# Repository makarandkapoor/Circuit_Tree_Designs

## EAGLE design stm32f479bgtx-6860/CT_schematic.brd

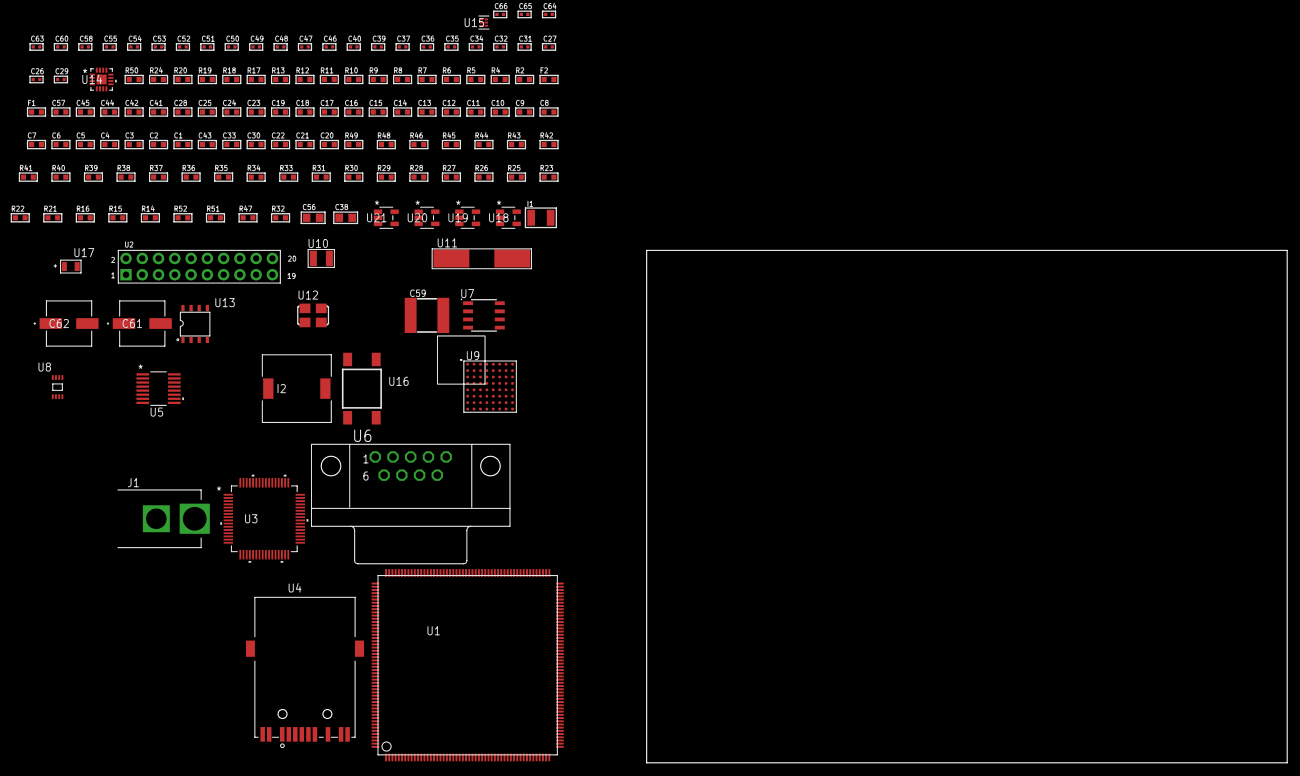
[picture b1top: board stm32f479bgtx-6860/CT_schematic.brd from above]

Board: 2 copper layers, 100.0 x 80.0 mm, 142 parts (0 on the bottom side), 151 nets, no tracks yet.

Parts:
C1, C24, C28, C41, C42, C44, C45, C57: 1e-06; C0603
C2, C3, C4, C5, C6, C7, C8, C9, C10, C11, C12, C13, C14, C15, C16, C17, C18, C19, C25: 1e-07; C0603
C20: 4.7e-06; C0603
C21, C22, C30, C33: 2.2e-06; C0603
C23: 1e-08; C0603
C26, C27: 1e-11; C0402
C29: 1.8e-08; C0402
C31, C34, C36, C37, C39, C40, C48, C50, C52, C58, C60: 1e-07; C0402
C32, C35, C46, C47, C49, C51, C53, C54, C55, C63, C64, C65, C66: 1e-08; C0402
C38, C56: 1e-05; C0805
C43: 2.2e-07; C0603
C59: 6.8e-05; 2220
C61, C62: 0.0001; EXV-9H
F1: 240.0; L0603
F2: 510.0; L0603
I1: 1e-05; L1210
I2: 3.8e-06; DR1040
J1: PJ-037B; PJ-037B_PACKAGE
R2: 1000.0; R0603
R4, R5, R6, R7: 4700.0; R0603
R8, R9, R10, R11, R12, R13: 2200.0; R0603
R14, R15, R16, R21, R22, R23, R25, R26, R27, R28, R29, R30, R31, R33, R34, R35, R36, R37, R38, R39, R40, R41, R42, R43, R44, R48, R49: 10000.0; R0603
R17, R18: 0.1; R0603
R19, R20: 200.0; R0603
R24: 1270.0; R0603
R32: 100000.0; R0603
R45: 20000.0; R0603
R46: 91000.0; R0603
R47: 300000.0; R0603
R50: 9100.0; R0603
R51: 680000.0; R0603
R52: 120000.0; R0603
U1: STM32F479BGT6; LQFP208
U2: arducam_ov2640; ARDUCAM
U3: BCM5221KPT; TQFP64_10X10MC
U4: 7498011122R
U5: LTC2804CGN-1#PBF; SSOP-16
U6: 182-009-113R531; 182-009-MALE
U7: AT24C02D-SSHM-T; AT24C02D
U8: 24AA128T-I/MNY; TDFN-8/6MM
U9: PC28F512P33BFD
U10: ABS07-32.768KHZ-7-T
U11: ABLS-25.000MHZ-B2F-T
U12: ASFL1-25MHZ-NCS; ASFL1
U13: idt74fct38072; IDT74FCT38072
U14: LTC3601EUD#PBF; QFN-16_EP
U15: TPS3895ADRYR; SON-6
U16: 4-1437565-2; SW_4-1437565-2
U17: Q65110A2395; LGM67K-G1J2-24-Z
U18, U19, U20, U21: nc7sz125m5x; NC7SZ125M5X

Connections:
CLK_CRYSTAL_U1_9: C26.1, U1.9, U10.1
CLK_CRYSTAL_U1_10: C27.1, U1.10, U10.2
CLK_CRYSTAL_U3_5: U3.5, U11.2
CLK_CRYSTAL_U3_6: U3.6, U11.1
CLK_U1_32: U1.32, U13.6
CLK_U2_8: U2.8, U13.7
CLK_U13_3: U12.3, U13.3
GND: C1.2, C2.2, C3.2, C4.2, C5.2, C6.2, C7.2, C8.2, C9.2, C10.2, C11.2, C12.2, C13.2, C14.2, C15.2, C16.2, C17.2, C18.2, C19.2, C20.2, C21.2, C22.2, C23.2, C24.2, C25.2, C26.2, C27.2, C28.2, C29.2, C30.2, C31.2, C32.2, C33.2, C34.2, C35.2, C36.2, C37.2, C38.2, C39.2, C40.2, C41.2, C42.2, C44.2, C45.2, C46.2, C47.2, C48.2, C49.2, C50.2, C51.2, C52.2, C53.2, C54.2, C55.2, C56.2, C57.2, C59.1, C59.2, C60.2, C61.2, C62.2, C63.2, C64.2, C65.2, C66.2, J1.2, R2.2, R16.2, R17.2, R18.2, R21.2, R23.2, R24.2, R26.2, R27.2, R28.2, R29.2, R30.2, R33.2, R35.2, R36.2, R38.2, R45.2, R47.2, R50.2, R52.2, U1.14, U1.25, U1.40, U1.51, U1.60, U1.72, U1.82, U1.93, U1.114, U1.122, U1.128, U1.136, U1.149, U1.170, U1.184, U1.202, U2.2, U2.20, U3.7, U3.24, U3.29, U3.32, U3.40, U3.45, U3.54, U3.63, U4.10, U4.12, U5.8, U6.5, U7.4, U8.4, U8.7, U9.B2, U9.H2, U9.H4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
NET_U1_34: R6.1, U1.34, U20.4
NET_U1_36: R12.1, U1.36, U3.42
NET_U1_42: C23.1, C24.1, F1.1, U1.41, U1.42
NET_U1_45: R13.1, U1.45, U3.41
NET_U1_48: R10.1, U1.48, U7.6
NET_U1_49: R11.1, U1.49, U7.5
NET_U1_63: R16.1, U1.63
NET_U1_92: C21.1, U1.92
NET_U1_148: C22.1, U1.148
NET_U1_195: R8.1, U1.195, U8.6
NET_U1_197: R15.1, U1.197
NET_U1_199: R9.1, U1.199, U8.5
NET_U1_203: R14.1, U1.203
NET_U1_206: U16.3, U16.4
NET_U2_19: R7.1, U2.19, U21.4
NET_U3_2: C33.1, C34.1, C35.1, U3.2, U3.55
NET_U3_9: R4.1, U3.9, U18.4
NET_U3_10: R25.1, U3.10
NET_U3_11: R26.1, U3.11
NET_U3_12: R27.1, U3.12
NET_U3_13: R28.1, U3.13
NET_U3_14: R29.1, U3.14
NET_U3_16: R23.1, U3.16
NET_U3_18: R31.1, U3.18
NET_U3_23: R24.1, U3.23
NET_U3_27: C30.1, C31.1, C32.1, U3.22, U3.27, U3.28
NET_U3_37: R30.1, U3.37
NET_U3_38: R21.1, U3.38
NET_U3_39: R22.1, U3.39
NET_U4_1: U3.31, U4.1
NET_U4_2: F2.2, U4.2
NET_U4_3: U3.30, U4.3
NET_U4_4: U3.26, U4.4
NET_U4_5: C29.1, F2.1, U4.2, U4.5
NET_U4_6: U3.25, U4.6
NET_U4_8: R18.1, U4.8
NET_U4_9: R19.1, U4.9
NET_U4_11: R20.1, U4.11
NET_U4_12: R19.2, U4.12
NET_U4_13: R17.1, U4.13, U4.14
NET_U5_6: C41.1, U5.6
NET_U5_7: C43.1, I1.2, U5.7
NET_U5_9: C42.1, U5.9
NET_U5_10: C43.2, U5.10
NET_U5_11: R32.1, U5.11
NET_U6_2: U5.1, U6.2
NET_U6_3: U5.3, U6.3
NET_U6_7: U5.2, U6.7
NET_U6_8: U5.4, U6.8
NET_U7_1: R34.1, U7.1
NET_U7_2: R35.1, U7.2
NET_U7_3: R36.1, U7.3
NET_U7_7: R33.1, U7.7
NET_U8_1: R37.1, U8.1
NET_U8_2: R38.1, U8.2
NET_U8_3: R39.1, U8.3
NET_U9_A4: C52.1, C53.1, U9.A4
NET_U9_C6: R43.1, U9.C6
NET_U9_D4: R5.1, U9.D4, U19.4
NET_U14_3: C58.2, I2.1, U14.3, U14.4
NET_U14_6: C58.1, U14.6
NET_U14_7: C57.1, U14.7, U14.12
NET_U14_10: R47.1, U14.10
NET_U14_11: R45.1, R46.1, U14.11
NET_U14_ATNET_3: I2.2, R46.2
NET_U15_1: R49.1, R50.1, U15.1
NET_U15_3: R51.2, R52.1, U15.3
NET_U15_4: R48.1, U15.4, U18.2, U19.2, U20.2, U21.2
NET_U16_1: R2.1, U16.1, U16.2
PROC_DCMI_D0: U1.99, U2.18
PROC_DCMI_D1: U1.100, U2.17
PROC_DCMI_D2: U1.101, U2.16
PROC_DCMI_D3: U1.102, U2.15
PROC_DCMI_D4: U1.152, U2.14
PROC_DCMI_D5: U1.205, U2.13
PROC_DCMI_D6: U1.207, U2.12
PROC_DCMI_D7: U1.208, U2.11
PROC_DCMI_D8: U1.96, U2.10
PROC_DCMI_D9: U1.97, U2.9
PROC_DCMI_HSYNC: U1.53, U2.6
PROC_DCMI_PIXCLK: U1.55, U2.7
PROC_DCMI_VSYNC: U1.178, U2.5
PROC_ETH_COL: U1.47, U3.61
PROC_ETH_CRS: U1.46, U3.62
PROC_ETH_RXD0: U1.57, U3.48
PROC_ETH_RXD1: U1.58, U3.47
PROC_ETH_RXD2: U1.61, U3.44
PROC_ETH_RX_CLK: U1.44, U3.50
PROC_ETH_RX_DV: U1.56, U3.49
PROC_ETH_RX_ER: U1.12, U3.51
PROC_ETH_TXD2: U1.37, U3.59
PROC_ETH_TX_CLK: U1.38, U3.53
PROC_FMC_A0: U1.16, U9.A1
PROC_FMC_A1: U1.17, U9.B1
PROC_FMC_A2: U1.18, U9.C1
PROC_FMC_A3: U1.22, U9.D1
PROC_FMC_A4: U1.23, U9.D2
PROC_FMC_A5: U1.24, U9.A2
PROC_FMC_A6: U1.71, U9.C2
PROC_FMC_A7: U1.74, U9.A3
PROC_FMC_A8: U1.75, U9.B3
PROC_FMC_A9: U1.76, U9.C3
PROC_FMC_A10: U1.77, U9.D3
PROC_FMC_A11: U1.78, U9.C4
PROC_FMC_A12: U1.129, U9.A5
PROC_FMC_A13: U1.130, U9.B5
PROC_FMC_A14: U1.131, U9.C5
PROC_FMC_A15: U1.132, U9.D7
PROC_FMC_A16: U1.111, U9.D8
PROC_FMC_A17: U1.112, U9.A7
PROC_FMC_A18: U1.113, U9.B7
PROC_FMC_A19: U1.2, U9.C7
PROC_FMC_A20: U1.3, U9.C8
PROC_FMC_A21: U1.4, U9.A8
PROC_FMC_A22: U1.5, U9.G1
PROC_FMC_A23: U1.1, U9.H8
PROC_FMC_A24: U1.182, U9.B6
PROC_FMC_CLK: U1.167, U9.E6
PROC_FMC_D0: U1.116, U9.F2
PROC_FMC_D1: U1.117, U9.E2
PROC_FMC_D2: U1.164, U9.G3
PROC_FMC_D3: U1.165, U9.E4
PROC_FMC_D4: U1.79, U9.E5
PROC_FMC_D5: U1.80, U9.G5
PROC_FMC_D6: U1.81, U9.G6
PROC_FMC_D7: U1.84, U9.H7
PROC_FMC_D8: U1.85, U9.E1
PROC_FMC_D9: U1.86, U9.E3
PROC_FMC_D10: U1.87, U9.F3
PROC_FMC_D11: U1.88, U9.F4
PROC_FMC_D12: U1.89, U9.F5
PROC_FMC_D13: U1.108, U9.H5
PROC_FMC_D14: U1.109, U9.G7
PROC_FMC_D15: U1.110, U9.E7
PROC_FMC_NE2: R41.1, U1.181, U9.B4
PROC_FMC_NL: R40.1, U1.196, U9.F6
PROC_FMC_NOE: R42.1, U1.168, U9.F8
PROC_FMC_NWAIT: U1.172, U9.F7
PROC_FMC_NWE: R44.1, U1.169, U9.G8
PROC_UART4_RX: U1.162, U5.16
PROC_UART4_TX: U1.43, U5.14
VCC_S1_9V2: C56.1, C61.1, C62.1, J1.1, U14.15, U14.16
VCC_TIER1_3V3: C1.1, C2.1, C3.1, C4.1, C5.1, C6.1, C7.1, C8.1, C9.1, C10.1, C11.1, C12.1, C13.1, C14.1, C15.1, C16.1, C17.1, C18.1, C19.1, C20.1, C25.1, C28.1, C36.1, C37.1, C38.1, C39.1, C40.1, C44.1, C45.1, C46.1, C47.1, C48.1, C49.1, C50.1, C51.1, C54.1, C55.1, C59.2, C60.1, C63.1, C64.1, C65.1, C66.1, F1.2, I1.1, I2.2, R4.2, R5.2, R6.2, R7.2, R8.2, R9.2, R10.2, R11.2, R12.2, R13.2, R14.2, R15.2, R22.2, R25.2, R31.2, R32.2, R34.2, R37.2, R39.2, R40.2, R41.2, R42.2, R43.2, R44.2, R46.2, R48.2, R49.2, R51.1, U1.6, U1.15, U1.26, U1.39, U1.52, U1.59, U1.73, U1.83, U1.94, U1.103, U1.115, U1.118, U1.137, U1.150, U1.158, U1.171, U1.185, U1.204, U2.1, U3.1, U3.3, U3.46, U5.5, U5.12, U7.8, U8.8, U9.A6, U9.D5, U9.D6, U9.G4, U9.H3, U12.4, U13.1, U13.2, U14.8, U15.6, U18.5, U19.5, U20.5, U21.5

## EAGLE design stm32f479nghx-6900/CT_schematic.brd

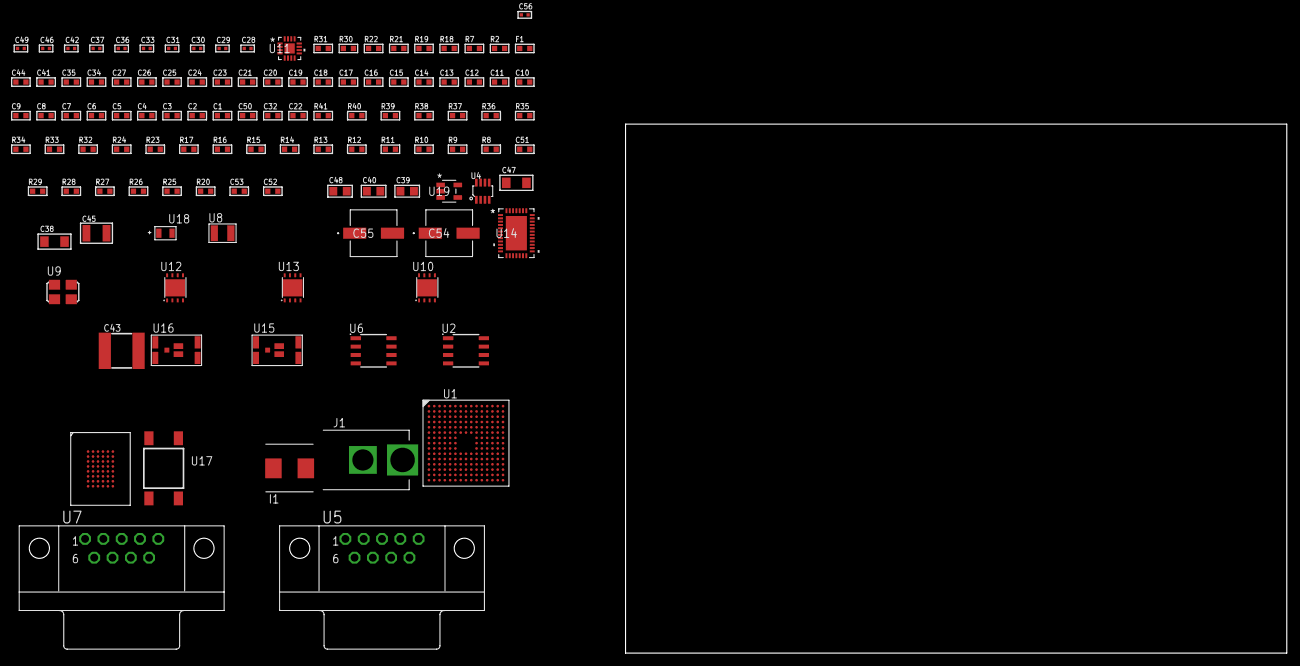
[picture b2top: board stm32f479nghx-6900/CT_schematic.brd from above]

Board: 2 copper layers, 100.0 x 80.0 mm, 114 parts (0 on the bottom side), 101 nets, no tracks yet.

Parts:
C1, C24, C34, C35, C41, C44: 1e-06; C0603
C2, C3, C4, C5, C6, C7, C8, C9, C10, C11, C12, C13, C14, C15, C16, C17, C18, C19, C20, C21, C25, C26, C27: 1e-07; C0603
C22: 4.7e-06; C0603
C23: 1e-08; C0603
C28, C29: 1e-11; C0402
C30, C36, C37, C46, C56: 1e-08; C0402
C31, C33, C42, C49: 1e-07; C0402
C32, C50: 2.2e-06; C0603
C38, C47: 1e-05; C1206
C39, C40, C48: 1e-05; C0805
C43: 6.8e-05; 2220
C45: 1e-05; C1210
C51: 2.45e-08; R0603
C52: 2.8258362168397e-09; R0603
C53: 7.105e-09; R0603
C54, C55: 0.0001; EXV-9H
F1: 240.0; L0603
I1: 3.3e-06; WE-HCI_7030/7040/7050
J1: PJ-037B; PJ-037B_PACKAGE
R2, R22, R31: 1000.0; R0603
R7: 4700.0; R0603
R8, R9, R10, R11, R12, R13, R14, R15, R16, R17, R32, R34, R35, R38, R39, R40: 10000.0; R0603
R18, R19: 120.0; R0603
R20, R26, R28, R29: 100000.0; R0603
R21, R30: 200.0; R0603
R23: 20000.0; R0603
R24: 91000.0; R0603
R25, R27: 300000.0; R0603
R33: 75000.0; R0603
R36, R37: 95300.0; R0603
R41: 62000.0; R0603
U1: STM32F479NGH6; TFBGA216
U2: AT25M02-SSHD-T; SOIC-8
U3: IS61WV102416BLL-10MLI
U4: MAX3051EKA+T; SOT-23-8
U5, U7: 182-009-113R531; 182-009-MALE
U6: MCP2562-E/SN; SOIC-8
U8: ABS07-32.768KHZ-7-T
U9: ASFL1-25MHZ-NCS; ASFL1
U10, U13: LP3878SDX-ADJ/NOPB; WSON-8
U11: LTC3601EUD#PBF; QFN-16_EP
U12: LP2951ACSDX/NOPB; WSON-8
U14: LTC2928CUHF#PBF; QFN-38_UHF
U15, U16: IRF8306MTRPbF; IRF8306MTRPBF
U17: 4-1437565-2; SW_4-1437565-2
U18: Q65110A2395; LGM67K-G1J2-24-Z
U19: nc7sz125m5x; NC7SZ125M5X

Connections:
CLK_CRYSTAL_U1_E1: C28.1, U1.E1, U8.1
CLK_CRYSTAL_U1_F1: C29.1, U1.F1, U8.2
CLK_U1_G1: U1.G1, U9.3
GND: C1.2, C2.2, C3.2, C4.2, C5.2, C6.2, C7.2, C8.2, C9.2, C10.2, C11.2, C12.2, C13.2, C14.2, C15.2, C16.2, C17.2, C18.2, C19.2, C20.2, C21.2, C22.2, C23.2, C24.2, C25.2, C26.2, C27.2, C28.2, C29.2, C30.2, C31.2, C32.2, C33.2, C34.2, C35.2, C36.2, C37.2, C38.2, C39.2, C40.2, C41.2, C43.1, C43.2, C44.2, C45.2, C46.2, C47.2, C48.2, C49.2, C50.2, C51.2, C52.2, C53.2, C54.2, C55.2, C56.2, J1.2, R2.2, R10.2, R22.2, R23.2, R25.2, R28.2, R31.2, R33.2, R36.2, R37.2, R38.2, R39.2, R40.2, U1.F2, U1.F6, U1.F7, U1.F8, U1.F9, U1.F10, U1.G6, U1.G10, U1.G12, U1.H6, U1.H10, U1.J6, U1.J10, U1.K6, U1.K7, U1.K8, U1.K9, U1.K10, U1.L6, U1.M1, U1.N1, U2.4, U3.D1, U3.E6, U4.2, U4.8, U5.5, U6.2, U6.8, U7.5, U9.2, U10.3, U10.PAD, U11.1, U11.9, U11.17, U12.3, U12.4, U12.PAD, U13.3, U13.PAD, U14.8, U14.9, U14.10, U14.12, U14.13, U14.24, U14.25, U14.30, U14.32, U14.39, U18.C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
NET_U1_E5: R8.1, U1.E5
NET_U1_E6: R9.1, U1.E6
NET_U1_E11: C27.1, U1.E11
NET_U1_J1: R7.1, U1.J1, U19.4
NET_U1_L5: R11.1, U1.L5
NET_U1_M5: R10.1, U1.M5
NET_U1_R1: C23.1, C24.1, F1.1, U1.P1, U1.R1
NET_U1_R15: U17.3, U17.4
NET_U2_3: R12.1, U2.3
NET_U2_7: R14.1, U2.7
NET_U3_A2: R16.1, U3.A2
NET_U3_B5: R15.1, U3.B5
NET_U3_G5: R17.1, U3.G5
NET_U4_6: R18.2, U4.6
NET_U5_2: R18.2, U4.6, U5.2
NET_U5_3: R18.1, U4.7, U5.3
NET_U6_6: R19.2, U6.6
NET_U7_2: R19.2, U6.6, U7.2
NET_U7_3: R19.1, U6.7, U7.3
NET_U10_1: C37.1, U10.1
NET_U10_6: R21.2, R22.1, U10.6
NET_U10_8: R20.1, U10.8
NET_U11_3: C42.2, I1.1, U11.3, U11.4
NET_U11_6: C42.1, U11.6
NET_U11_7: C41.1, U11.7, U11.12
NET_U11_10: R25.1, U11.10
NET_U11_11: R23.1, R24.1, U11.11
NET_U11_ATNET_3: I1.2, R24.2
NET_U12_5: R26.1, U12.5
NET_U12_7: R27.2, R28.1, U12.7
NET_U13_1: C46.1, U13.1
NET_U13_6: R30.2, R31.1, U13.6
NET_U13_8: R29.1, U13.8
NET_U14_3: R39.1, U14.3
NET_U14_6: R36.1, U14.6
NET_U14_7: R37.1, U14.7
NET_U14_16: R38.1, R41.1, U14.16
NET_U14_18: R35.1, U14.18
NET_U14_19: R34.1, U14.19, U14.20
NET_U14_21: R32.1, R33.1, U14.21, U19.2
NET_U14_22: C49.1, R32.2, R34.2, R35.2, U14.11, U14.22
NET_U14_26: C52.1, U14.26
NET_U14_27: C51.1, U14.27
NET_U14_28: C53.1, U14.28
NET_U14_38: R40.1, U14.38
NET_U15_3: U14.2, U15.3
NET_U16_3: U14.37, U16.3
NET_U17_1: R2.1, U17.1, U17.2
PROC_CAN1_RX: U1.A7, U6.4
PROC_CAN1_TX: U1.B4, U6.1
PROC_CAN2_RX: U1.L13, U4.4
PROC_CAN2_TX: U1.B6, U4.1
PROC_FMC_A0: U1.D2, U3.A3
PROC_FMC_A1: U1.E2, U3.A4
PROC_FMC_A2: U1.G2, U3.A5
PROC_FMC_A3: U1.H2, U3.B3
PROC_FMC_A4: U1.J2, U3.B4
PROC_FMC_A5: U1.K3, U3.C3
PROC_FMC_A6: U1.M6, U3.C4
PROC_FMC_A7: U1.N6, U3.D4
PROC_FMC_A8: U1.P6, U3.H2
PROC_FMC_A9: U1.M8, U3.H3
PROC_FMC_A10: U1.N7, U3.H4
PROC_FMC_A11: U1.M7, U3.H5
PROC_FMC_A12: U1.M13, U3.G3
PROC_FMC_A13: U1.M12, U3.G4
PROC_FMC_A14: U1.N12, U3.F3
PROC_FMC_A15: U1.N11, U3.F4
PROC_FMC_A16: U1.N10, U3.E4
PROC_FMC_A17: U1.M10, U3.D3
PROC_FMC_A18: U1.M11, U3.H1
PROC_FMC_A19: U1.A2, U3.G2
PROC_FMC_D0: U1.L12, U3.B6
PROC_FMC_D1: U1.K13, U3.C5
PROC_FMC_D2: U1.B12, U3.C6
PROC_FMC_D3: U1.C12, U3.D5
PROC_FMC_D4: U1.R8, U3.E5
PROC_FMC_D5: U1.N9, U3.F5
PROC_FMC_D6: U1.P9, U3.F6
PROC_FMC_D7: U1.R9, U3.G6
PROC_FMC_D8: U1.P10, U3.B1
PROC_FMC_D9: U1.R10, U3.C1
PROC_FMC_D10: U1.R12, U3.C2
PROC_FMC_D11: U1.P11, U3.D2
PROC_FMC_D12: U1.R11, U3.E2
PROC_FMC_D13: U1.L15, U3.F2
PROC_FMC_D14: U1.L14, U3.F1
PROC_FMC_D15: U1.K15, U3.G1
PROC_FMC_NBL0: U1.A6, U3.A1
PROC_SPI1_NSS: R13.1, U2.1
VCC_7V9: C50.1, C54.1, C55.1, J1.1, R41.2, U14.23, U15.1, U15.2, U15.6, U15.7, U16.1, U16.2, U16.6, U16.7
VCC_S1_7V9: C38.1, C40.1, C44.1, R20.2, U10.4, U11.15, U11.16, U12.8, U15.4, U15.5
VCC_S2_7V9: C47.1, R29.2, U13.4, U16.4, U16.5
VCC_TIER1_1V2: C26.1, C39.1, R21.1, U1.L11, U10.5
VCC_TIER1_3V3: C1.1, C2.1, C3.1, C4.1, C5.1, C6.1, C7.1, C8.1, C9.1, C10.1, C11.1, C12.1, C13.1, C14.1, C15.1, C16.1, C17.1, C18.1, C19.1, C20.1, C21.1, C22.1, C25.1, C30.1, C31.1, C32.1, C33.1, C35.1, C36.1, C43.2, C56.1, F1.2, I1.2, R7.2, R8.2, R9.2, R11.2, R12.2, R13.2, R14.2, R15.2, R16.2, R17.2, R24.2, U1.C1, U1.E7, U1.E8, U1.E9, U1.E10, U1.F4, U1.F5, U1.F11, U1.G5, U1.G11, U1.H5, U1.H11, U1.J5, U1.J11, U1.K5, U1.K11, U1.L7, U1.L8, U1.L9, U1.L10, U2.8, U3.D6, U3.E1, U4.3, U6.5, U9.4, U11.8, U19.5
VCC_TIER1_5V0: C34.1, C45.1, R26.2, R27.1, U6.3, U12.1
VCC_TIER2_1V2: C48.1, R30.1, U13.5

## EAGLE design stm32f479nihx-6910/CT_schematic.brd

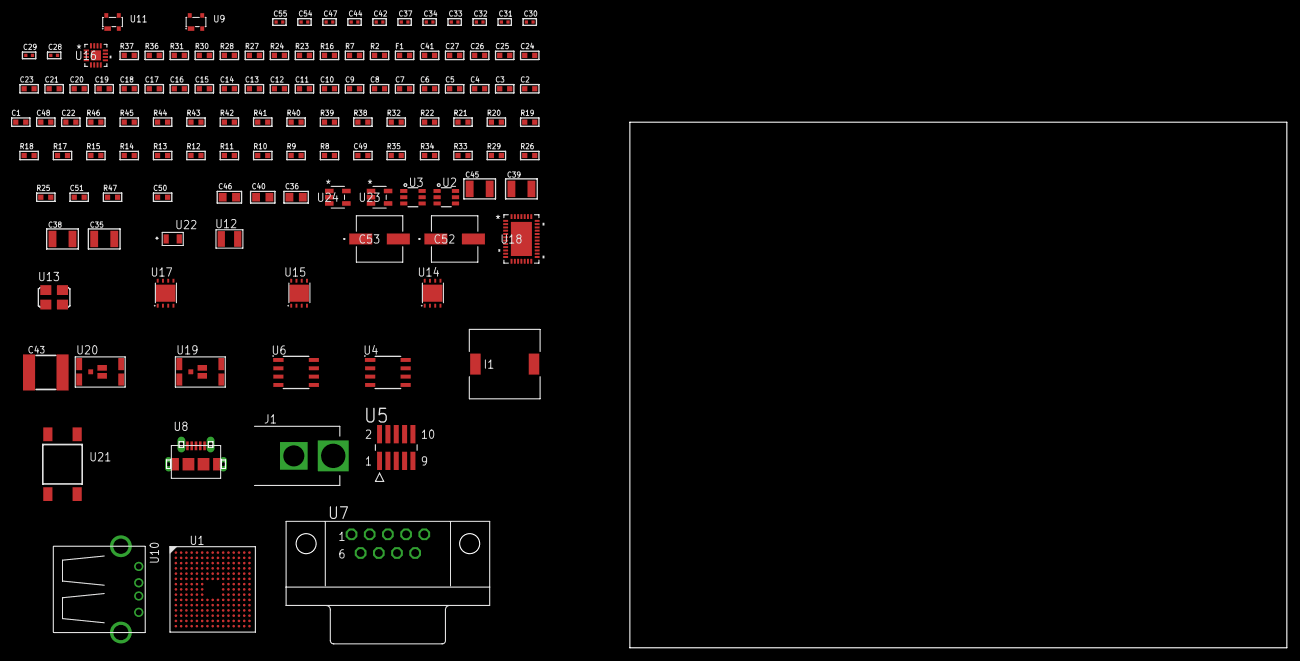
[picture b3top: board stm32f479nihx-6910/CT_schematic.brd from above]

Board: 2 copper layers, 124 parts (0 on the bottom side), 80 nets, no tracks yet.

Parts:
C1, C24, C41: 1e-06; C0603
C2, C3, C4, C5, C6, C7, C8, C9, C10, C11, C12, C13, C14, C15, C16, C17, C18, C19, C20, C21, C25, C26, C27: 1e-07; C0603
C22: 4.7e-06; C0603
C23: 1e-08; C0603
C28, C29: 1e-11; C0402
C30, C33, C34, C37, C44, C54, C55: 1e-08; C0402
C31, C32, C42, C47: 1e-07; C0402
C35, C38, C39, C45: 1e-05; C1210
C36, C40, C46: 1e-05; C0805
C43: 6.8e-05; 2220
C48: 2.2e-06; C0603
C49: 2.45e-08; R0603
C50: 2.8258362168397e-09; R0603
C51: 7.105e-09; R0603
C52, C53: 0.0001; EXV-9H
F1: 240.0; L0603
I1: 7e-06; DR1040
J1: PJ-037B; PJ-037B_PACKAGE
R2, R28, R31, R37: 1000.0; R0603
R7: 4700.0; R0603
R8, R9: 47000.0; R0603
R10, R11, R12, R13, R14, R15, R17, R18, R19, R20, R21, R22, R38, R40, R41, R44, R45, R46: 10000.0; R0603
R16: 1270.0; R0603
R23: 5.0; R0603
R24: 120.0; R0603
R25: 470000.0; R0603
R26, R29, R35: 100000.0; R0603
R27, R36: 200.0; R0603
R30: 2231.0; R0603
R32: 20000.0; R0603
R33: 150000.0; R0603
R34: 300000.0; R0603
R39: 75000.0; R0603
R42, R43: 95300.0; R0603
R47: 113145.45454545; R0603
U1: STM32F479NIH6; TFBGA216
U2, U3: MAX4995AAUT+T; SOT-23-6
U4: AT25160B-SSHL-T; SOIC-8
U5: FTSH-105-01-L-DV-K; SAMTEC_FTSH-105-01-L-DV-K
U6: SN65HVD230D; SOIC-8
U7: 182-009-113R531; 182-009-MALE
U8: 47590-0001; MICRO_USB_AB
U9, U11: prtr5v0u2ax; SOT143B
U10: 61400416021; USB-A-H
U12: ABS07-32.768KHZ-7-T
U13: ASFL1-25MHZ-NCS; ASFL1
U14, U15, U17: LP3878SDX-ADJ/NOPB; WSON-8
U16: LTC3601EUD#PBF; QFN-16_EP
U18: LTC2928CUHF#PBF; QFN-38_UHF
U19, U20: IRF8306MTRPbF; IRF8306MTRPBF
U21: 4-1437565-2; SW_4-1437565-2
U22: Q65110A2395; LGM67K-G1J2-24-Z
U23, U24: nc7sz125m5x; NC7SZ125M5X

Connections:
CLK_CRYSTAL_U1_E1: C28.1, U1.E1, U12.1
CLK_CRYSTAL_U1_F1: C29.1, U1.F1, U12.2
CLK_U1_G1: U1.G1, U13.3
GND: C1.2, C2.2, C3.2, C4.2, C5.2, C6.2, C7.2, C8.2, C9.2, C10.2, C11.2, C12.2, C13.2, C14.2, C15.2, C16.2, C17.2, C18.2, C19.2, C20.2, C21.2, C22.2, C23.2, C24.2, C25.2, C26.2, C27.2, C28.2, C29.2, C30.2, C31.2, C32.2, C33.2, C34.2, C35.2, C36.2, C37.2, C38.2, C39.2, C40.2, C41.2, C43.1, C43.2, C44.2, C45.2, C46.2, C47.2, C48.2, C49.2, C50.2, C51.2, C52.2, C53.2, C54.2, C55.2, J1.2, R2.2, R8.2, R9.2, R15.2, R16.2, R23.2, R25.2, R28.2, R31.2, R32.2, R34.2, R37.2, R39.2, R42.2, R43.2, R44.2, R45.2, R46.2, U1.F2, U1.F6, U1.F7, U1.F8, U1.F9, U1.F10, U1.G6, U1.G10, U1.G12, U1.H6, U1.H10, U1.J6, U1.J10, U1.K6, U1.K7, U1.K8, U1.K9, U1.K10, U1.L6, U1.L13, U1.M1, U1.N1, U2.2, U3.2, U4.4, U5.3, U5.5, U6.2, U7.5, U8.5, U8.6, U8.7, U8.8, U8.9, U9.1, U10.4, U10.5, U10.6, U11.1, U13.2, U14.3, U14.PAD, U15.3, U15.PAD, U16.1, U16.9, U16.17, U17.3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
NET_U1_E5: R10.1, U1.E5
NET_U1_E6: R11.1, U1.E6
NET_U1_E11: C27.1, U1.E11
NET_U1_J1: R7.1, U1.J1, U24.4
NET_U1_L5: R13.1, U1.L5
NET_U1_L13: R16.1, U1.L13
NET_U1_M5: R12.1, U1.M5
NET_U1_R1: C23.1, C24.1, F1.1, U1.P1, U1.R1
NET_U1_R13: U21.3, U21.4
NET_U2_3: R8.1, U2.3
NET_U3_3: R9.1, U3.3
NET_U4_3: R17.1, U4.3
NET_U4_7: R19.1, U4.7
NET_U5_9: R23.1, U5.9
NET_U6_6: R24.2, U6.6
NET_U6_8: R25.1, U6.8
NET_U7_2: R24.2, U6.6, U7.2
NET_U7_3: R24.1, U6.7, U7.3
NET_U14_1: C34.1, U14.1
NET_U14_6: R27.2, R28.1, U14.6
NET_U14_8: R26.1, U14.8
NET_U15_1: C37.1, U15.1
NET_U15_6: R30.2, R31.1, U15.6
NET_U15_8: R29.1, U15.8
NET_U16_3: C42.2, I1.1, U16.3, U16.4
NET_U16_6: C42.1, U16.6
NET_U16_7: C41.1, U16.7, U16.12
NET_U16_10: R34.1, U16.10
NET_U16_11: R32.1, R33.1, U16.11
NET_U16_ATNET_3: I1.2, R33.2
NET_U17_1: C44.1, U17.1
NET_U17_6: R36.2, R37.1, U17.6
NET_U17_8: R35.1, U17.8
NET_U18_3: R45.1, U18.3
NET_U18_6: R42.1, U18.6
NET_U18_7: R43.1, U18.7
NET_U18_16: R44.1, R47.1, U18.16
NET_U18_18: R41.1, U18.18
NET_U18_19: R40.1, U18.19, U18.20
NET_U18_21: R38.1, R39.1, U18.21, U23.4, U24.2
NET_U18_22: C47.1, R38.2, R40.2, R41.2, U18.11, U18.22
NET_U18_26: C50.1, U18.26
NET_U18_27: C49.1, U18.27
NET_U18_28: C51.1, U18.28
NET_U18_38: R46.1, U18.38
NET_U19_3: U18.2, U19.3
NET_U20_3: U18.37, U20.3
NET_U21_1: R2.1, U21.1, U21.2
PROC_CAN1_RX: U1.A7, U6.4
PROC_CAN1_TX: U1.B4, U6.1
PROC_GPIO_TO_U1_USB_FAULT: R14.1, U1.A2, U2.6
PROC_GPIO_TO_U1_USB_FAULT2: U1.A4, U3.6
PROC_GPIO_TO_U1_VBUS_EN: R15.1, U1.A1, U2.4
PROC_GPIO_TO_U1_VBUS_EN2: U1.A3, U3.4
PROC_SPI1_MISO: U1.A9, U4.2
PROC_SPI1_MOSI: U1.A8, U4.5
PROC_SPI1_NSS: R18.1, U1.A13, U4.1
PROC_SPI1_SCK: U1.P4, U4.6
PROC_SYS_JTCK_SWCLK: R21.1, U1.A14, U5.4
PROC_SYS_JTDO_SWO: U1.A10, U5.6
PROC_SYS_JTMS_SWDIO: R22.1, U1.A15, U5.2
PROC_USB_OTG_FS_DM: U1.C15, U8.2, U9.3
PROC_USB_OTG_FS_DP: U1.B15, U8.3, U9.2
PROC_USB_OTG_FS_ID: U1.D15, U8.4
PROC_USB_OTG_FS_VBUS: U1.E15, U2.1, U8.1, U9.4
PROC_USB_OTG_HS_DM: U1.R14, U10.2, U11.3
PROC_USB_OTG_HS_DP: U1.R15, U10.3, U11.2
PROC_USB_OTG_HS_VBUS: U1.K14, U3.1, U10.1, U11.4
RST_OUT_U5_JTAG_RST_B: R20.1, U5.10, U23.1
VCC_13V8: C48.1, C52.1, C53.1, J1.1, R47.2, U18.23, U19.1, U19.2, U19.6, U19.7, U20.1, U20.2, U20.6, U20.7
VCC_S1_13V8: C35.1, C38.1, C40.1, R26.2, R29.2, U14.4, U15.4, U16.15, U16.16, U19.4, U19.5
VCC_S2_13V8: C45.1, R35.2, U17.4, U20.4, U20.5
VCC_TIER1_1V2: C26.1, C36.1, R27.1, U1.L11, U14.5
VCC_TIER1_3V3: C1.1, C2.1, C3.1, C4.1, C5.1, C6.1, C7.1, C8.1, C9.1, C10.1, C11.1, C12.1, C13.1, C14.1, C15.1, C16.1, C17.1, C18.1, C19.1, C20.1, C21.1, C22.1, C25.1, C30.1, C31.1, C32.1, C33.1, C39.1, C54.1, C55.1, F1.2, R7.2, R10.2, R11.2, R12.2, R13.2, R14.2, R17.2, R18.2, R19.2, R20.2, R21.2, R22.2, R30.1, U1.C1, U1.E7, U1.E8, U1.E9, U1.E10, U1.F4, U1.F5, U1.F11, U1.G5, U1.G11, U1.H5, U1.H11, U1.J5, U1.J11, U1.K5, U1.K11, U1.L7, U1.L8, U1.L9, U1.L10, U4.8, U5.1, U6.3, U13.4, U15.5, U23.5, U24.5
VCC_TIER1_5V0: C43.2, I1.2, R33.2, U2.5, U3.5, U16.8
VCC_TIER2_1V2: C46.1, R36.1, U17.5

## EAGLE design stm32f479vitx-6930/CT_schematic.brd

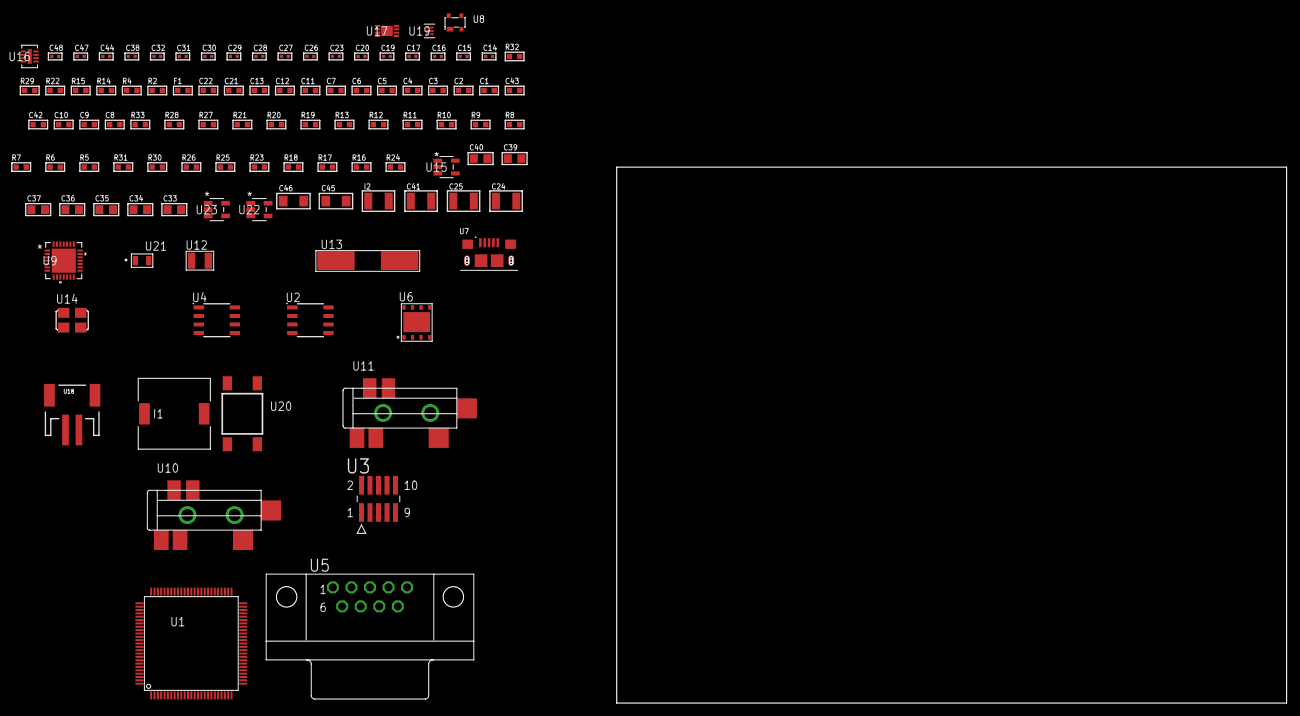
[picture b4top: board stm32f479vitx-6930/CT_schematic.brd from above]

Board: 2 copper layers, 122.6 x 80.0 mm, 104 parts (0 on the bottom side), 63 nets, no tracks yet.

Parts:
C1, C12, C21, C22: 1e-06; C0603
C2, C3, C4, C5, C6, C7, C13: 1e-07; C0603
C8: 4.7e-06; C0603
C9, C10, C42: 2.2e-06; C0603
C11: 1e-08; C0603
C14, C15, C16, C17: 1e-11; C0402
C19, C38, C47, C48: 1e-08; C0402
C20, C23, C28, C29, C30, C31, C32, C44: 1e-07; C0402
C24, C25: 2.2e-05; C1210
C26, C27: 1e-09; C0402
C33, C34, C35, C36, C37, C39, C40: 1e-05; C0805
C41: 1e-05; C1210
C43: 2.2e-07; C0603
C45, C46: 1e-05; C1206
F1: 240.0; L0603
I1: 2.5e-06; DR1040
I2: 1e-05; L1210
R2: 1000.0; R0603
R4: 4700.0; R0603
R5, R6, R7, R8, R9, R10, R11, R12, R13, R27, R28, R33: 10000.0; R0603
R14: 5.0; R0603
R15: 120.0; R0603
R16, R17, R18, R25: 100000.0; R0603
R19, R20, R21: 47000.0; R0603
R22: 680.0; R0603
R23: 220000.0; R0603
R24: 1000000.0; R0603
R26: 560000.0; R0603
R29: 9100.0; R0603
R30: 680000.0; R0603
R31: 120000.0; R0603
R32: 2000.0; R0603
U1: STM32F479VIT6; LQFP100
U2: AT25M01-SSHM-T; SOIC-8
U3: FTSH-105-01-L-DV-K; SAMTEC_FTSH-105-01-L-DV-K
U4: MCP2562-E/SN; SOIC-8
U5: 182-009-113R531; 182-009-MALE
U6: SST26VF032B-104I/MF; WFDN-8
U7: 10118193-0001LF; FCI_10118193-0001LF
U8: prtr5v0u2ax; SOT143B
U9: WM8731CLSEFL; QFN-28
U10, U11: SJ-43515TS-SMT-TR
U12: ABS07-32.768KHZ-7-T
U13: ABLS-25.000MHZ-B2F-T
U14: ASFL1-12.288MHZ-EC-T; ASFL1
U15: ltc3406es5; TSOT-23-5
U16: LT3494AEDDB#TRMPBF; DFN-8_DDB
U17: MCP73831T-2ACI/MC; DFN8_2X3MC
U18: S2B-PH-SM4-TB(LF)(SN); JST-2-SMD
U19: TPS3895ADRYR; SON-6
U20: 4-1437565-2; SW_4-1437565-2
U21: Q65110A2395; LGM67K-G1J2-24-Z
U22, U23: nc7sz125m5x; NC7SZ125M5X

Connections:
CLK_CRYSTAL_U1_5: C14.1, U1.5, U12.1
CLK_CRYSTAL_U1_6: C15.1, U1.6, U12.2
CLK_CRYSTAL_U1_9: C16.1, U1.9, U13.1
CLK_CRYSTAL_U1_10: C17.1, U1.10, U13.2
CLK_U9_1: U9.1, U14.3
GND: C1.2, C2.2, C3.2, C4.2, C5.2, C6.2, C7.2, C8.2, C9.2, C10.2, C11.2, C12.2, C13.2, C14.2, C15.2, C16.2, C17.2, C19.2, C20.2, C21.2, C22.2, C23.2, C27.2, C28.2, C29.2, C30.2, C31.2, C32.2, C33.2, C34.2, C35.2, C36.2, C37.2, C38.2, C39.2, C40.1, C40.2, C41.2, C42.2, C43.2, C44.2, C45.2, C46.2, C47.2, C48.2, R2.2, R13.2, R14.2, R19.2, R20.2, R21.2, R23.2, R29.2, R31.2, R32.2, U1.2, U1.7, U1.16, U1.23, U1.44, U1.59, U1.78, U2.4, U3.3, U3.5, U4.2, U4.8, U5.5, U6.4, U6.9, U7.5, U7.6, U7.7, U7.8, U7.9, U8.1, U9.4, U9.15, U9.19, U9.25, U9.26, U9.29, U10.1, U11.1, U14.2, U15.2, U16.2, U16.9, U17.6, U17.9, U18.2, U19.2, U21.C, U22.2, U22.3, U23.1, U23.3
INPUT_USBPOWER_5V: C45.1, R33.2, U7.1, U8.4, U17.1, U17.2
NET_U1_11: R4.1, U1.11, U23.4
NET_U1_18: C11.1, C12.1, F1.1, U1.17, U1.18
NET_U1_31: R6.1, U1.31
NET_U1_43: C9.1, U1.43
NET_U1_76: C10.1, U1.76
NET_U1_97: R5.1, U1.97
NET_U1_99: U20.3, U20.4
NET_U2_3: R7.1, U2.3
NET_U2_7: R9.1, U2.7
NET_U3_9: R14.1, U3.9
NET_U4_6: R15.2, U4.6
NET_U5_2: R15.2, U4.6, U5.2
NET_U5_3: R15.1, U4.7, U5.3
NET_U9_20: C32.1, C37.1, U9.20
NET_U10_2: C25.1, R20.1, U10.2
NET_U10_5: C24.1, R19.1, U10.5
NET_U11_5: C26.1, C27.1, R21.1, R22.1, U11.5
NET_U15_3: I1.1, U15.3
NET_U15_5: R23.1, R24.1, U15.5
NET_U15_ATNET_3: I1.2, R24.2
NET_U16_1: I2.1, U16.1
NET_U16_5: R25.1, U16.5
NET_U16_6: R26.1, U16.6
NET_U16_8: C43.1, U16.8
NET_U17_5: R33.1, U17.5
NET_U17_8: R32.1, U17.8
NET_U19_1: R28.1, R29.1, U19.1
NET_U19_3: R30.2, R31.1, U19.3
NET_U19_4: R27.1, U19.4, U22.4, U23.2
NET_U20_1: R2.1, U20.1, U20.2
PROC_CAN1_RX: U1.84, U4.4
PROC_CAN1_TX: U1.85, U4.1
PROC_I2S2_CK: U1.47, U9.7
PROC_I2S2_EXT_SD: U1.14, U9.10
PROC_I2S2_SD: U1.13, U9.8
PROC_I2S2_WS: U1.46, U9.9, U9.11
PROC_QUADSPI_BK1_IO0: U1.69, U6.5
PROC_QUADSPI_BK1_IO1: U1.81, U6.2
PROC_QUADSPI_BK1_IO2: R17.1, U1.1, U6.3
PROC_QUADSPI_BK1_IO3: R18.1, U1.20, U6.7
PROC_QUADSPI_BK1_NCS: R16.1, U1.41, U6.1
PROC_QUADSPI_CLK: U1.28, U6.6
PROC_SPI1_MISO: U1.27, U2.2
PROC_SPI1_MOSI: U1.94, U2.5
PROC_SPI1_NSS: R8.1, U1.25, U2.1
PROC_SPI1_SCK: U1.26, U2.6
PROC_SYS_JTCK_SWCLK: R13.1, U1.79, U3.4
PROC_SYS_JTDI: R11.1, U1.80, U3.8
PROC_SYS_JTDO_SWO: U1.92, U3.6
PROC_SYS_JTMS_SWDIO: R12.1, U1.75, U3.2
PROC_USB_OTG_FS_DM: U7.2, U8.3
PROC_USB_OTG_FS_DP: U7.3, U8.2
RST_OUT_U3_JTAG_RST_B: R10.1, U3.10, U22.1
VCC_S1_3V7: C39.1, C41.1, C46.1, I2.2, R25.2, U15.4, U16.3, U16.4, U17.3, U17.4, U18.1
VCC_TIER1_3V3: C1.1, C2.1, C3.1, C4.1, C5.1, C6.1, C7.1, C8.1, C13.1, C19.1, C20.1, C22.1, C23.1, C28.1, C29.1, C30.1, C31.1, C33.1, C34.1, C35.1, C36.1, C38.1, C40.2, C44.1, C47.1, C48.1, F1.2, I1.2, R4.2, R5.2, R6.2, R7.2, R8.2, R9.2, R10.2, R11.2, R12.2, R16.2, R17.2, R18.2, R24.2, R27.2, R28.2, R30.1, U1.3, U1.8, U1.24, U1.45, U1.55, U1.65, U1.77, U1.100, U2.8, U3.1, U4.5, U6.8, U9.3, U9.5, U9.12, U9.18, U14.4, U19.6, U22.5, U23.5
VCC_TIER1_5V0: C21.1, C42.1, R26.2, U4.3, U16.7

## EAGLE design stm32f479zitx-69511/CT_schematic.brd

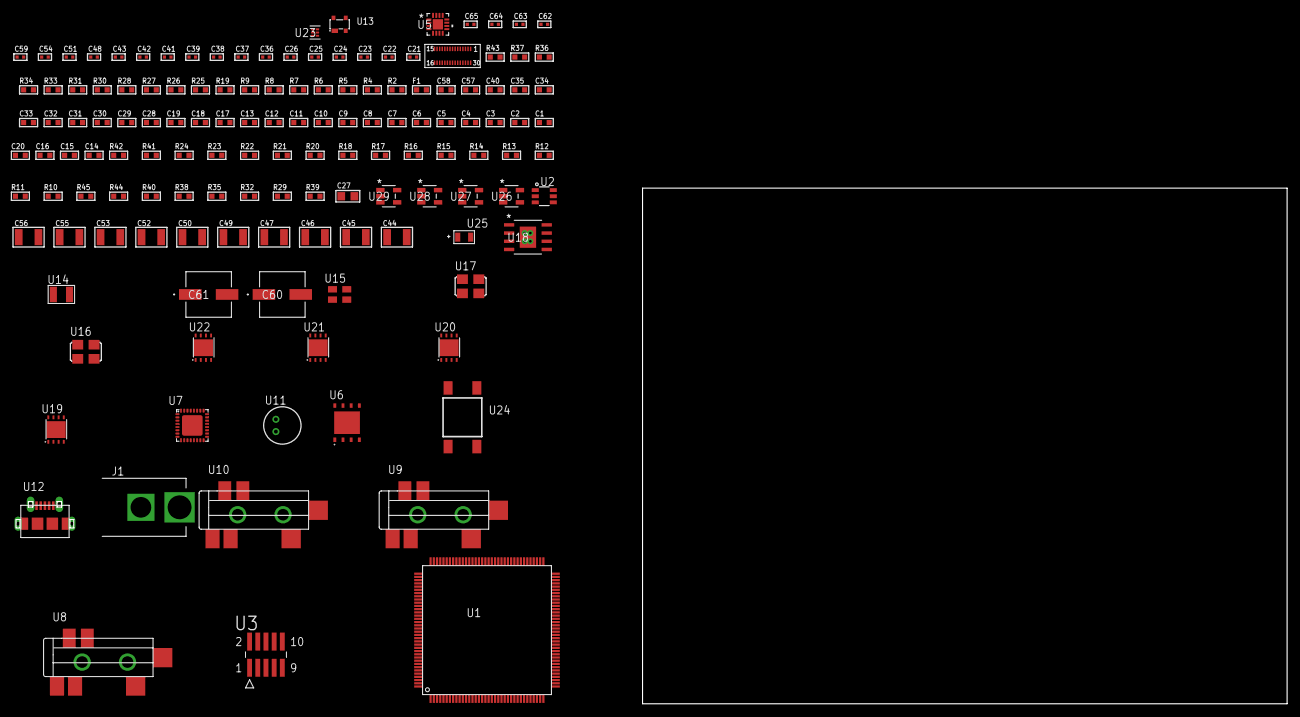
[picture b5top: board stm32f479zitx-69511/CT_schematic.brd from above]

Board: 2 copper layers, 139 parts (0 on the bottom side), 85 nets, no tracks yet.

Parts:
C1, C18, C28, C29, C30, C31, C32, C33, C34, C35, C40: 1e-06; C0603
C2, C3, C4, C5, C6, C7, C8, C9, C10, C11, C12, C13, C19: 1e-07; C0603
C14: 4.7e-06; C0603
C15, C16, C20: 2.2e-06; C0603
C17: 1e-08; C0603
C21, C22, C23, C24, C25, C26, C36, C37, C38, C39, C59: 1e-07; C0402
C27: 4.7e-06; C0805
C41, C42, C43, C48, C51, C54, C62, C63, C64, C65: 1e-08; C0402
C44, C45, C46, C47, C49, C50, C52, C53, C55, C56: 1e-05; C1210
C57: 8e-07; R0603
C58: 8e-06; R0603
C60, C61: 0.0001; EXV-9H
F1: 240.0; L0603
J1: PJ-037B; PJ-037B_PACKAGE
R2, R31, R34, R37: 1000.0; R0603
R4, R5, R6: 4700.0; R0603
R7, R8, R9, R28: 2200.0; R0603
R10: 47000.0; R0603
R11, R12, R13, R14, R15, R16, R17, R18, R20, R21, R22, R23, R24, R41, R42: 10000.0; R0603
R19: 5.0; R0603
R25, R26: 1270.0; R0603
R27: 910.0; R0603
R29, R32, R35, R38, R40: 100000.0; R0603
R30: 1800.0; R0603
R33: 2231.0; R0603
R36: 3900.0; R0603
R39: 842943.08; R0603
R43: 9100.0; R0603
R44: 680000.0; R0603
R45: 120000.0; R0603
U1: STM32F479ZIT6; LQFP144
U2: MAX4995AAUT+T; SOT-23-6
U3: FTSH-105-01-L-DV-K; SAMTEC_FTSH-105-01-L-DV-K
U4: LH430WV2-SD01
U5: M41T65Q6F; M41T65_QFN-16
U6: MX25R6435FZAIH0; WSON-8-PAD
U7: SGTL5000XNAA3; QFN-32
U8, U9, U10: SJ-43515TS-SMT-TR
U11: WM-64PCT; WM-64PC
U12: 47590-0001; MICRO_USB_AB
U13: prtr5v0u2ax; SOT143B
U14: ABS07-32.768KHZ-7-T
U15: ASEK-32.768KHz-ECST; ASEK
U16: ASFL-24.57MHZ-NCS; ASFL1
U17: ASFL1-25MHZ-NCS; ASFL1
U18: MIC5234YME; SOIC-8_EP
U19, U20, U21: LP3878SDX-ADJ/NOPB; WSON-8
U22: LP2951ACSDX/NOPB; WSON-8
U23: TPS3895ADRYR; SON-6
U24: 4-1437565-2; SW_4-1437565-2
U25: Q65110A2395; LGM67K-G1J2-24-Z
U26, U27, U28, U29: nc7sz125m5x; NC7SZ125M5X

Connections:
CLK_CRYSTAL_U5_1: U5.1, U14.1
CLK_CRYSTAL_U5_2: U5.2, U14.2
CLK_U1_7: U1.7, U15.3
CLK_U1_18: U1.18, U17.3
CLK_U7_21: U7.21, U16.3
GND: C1.2, C2.2, C3.2, C4.2, C5.2, C6.2, C7.2, C8.2, C9.2, C10.2, C11.2, C12.2, C13.2, C14.2, C15.2, C16.2, C17.2, C18.2, C19.2, C21.2, C22.2, C23.2, C24.2, C25.2, C26.2, C27.2, C28.2, C36.2, C37.2, C38.2, C39.2, C40.2, C41.2, C42.2, C43.2, C44.2, C45.2, C46.2, C47.2, C48.2, C49.2, C50.2, C51.2, C52.2, C53.2, C54.2, C55.2, C56.2, C57.2, C58.2, C59.2, C60.2, C61.2, C62.2, C63.2, C64.2, C65.2, J1.2, R2.2, R10.2, R13.2, R15.2, R19.2, R20.2, R26.2, R28.2, R31.2, R34.2, R37.2, R40.2, R43.2, R45.2, U1.15, U1.26, U1.33, U1.55, U1.76, U1.109, U1.122, U1.129, U2.2, U3.3, U3.5, U4.1, U4.6, U4.9, U4.12, U4.15, U4.17, U4.18, U4.19, U4.24, U4.27, U5.3, U5.5, U5.17, U6.4, U6.PAD, U7.1, U7.3, U7.7, U7.EXP, U9.1, U10.1, U11.2, U12.5, U12.6, U12.7, U12.8, U12.9, U13.1, U15.2, U16.2, U17.2, U18.7, U18.EPAD, U19.3, U19.PAD, U20.3, U20.PAD, U21.3, U21.PAD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
NET_U1_20: R6.1, U1.20, U29.4
NET_U1_28: C17.1, C18.1, F1.1, U1.27, U1.28
NET_U1_43: R13.1, U1.43
NET_U1_65: C15.1, U1.65
NET_U1_84: C20.2, U1.84
NET_U1_87: C20.1, U1.81, U1.87
NET_U1_108: C16.1, U1.108
NET_U1_135: R7.1, U1.135, U5.10
NET_U1_136: R8.1, U1.136, U5.9
NET_U1_137: R12.1, U1.137
NET_U1_141: U24.3, U24.4
NET_U1_142: R11.1, U1.142
NET_U2_3: R10.1, U2.3
NET_U3_9: R19.1, U3.9
NET_U4_4: R4.1, U4.4, U27.4
NET_U4_20: R20.1, U4.20
NET_U5_4: R21.1, U5.4
NET_U5_11: R22.1, U5.11
NET_U6_7: R5.1, U1.30, U6.7, U28.4
NET_U7_10: C39.1, U7.10
NET_U7_29: R25.1, U7.29
NET_U7_31: R26.1, U7.31
NET_U8_1: U7.4, U8.1
NET_U8_2: U7.2, U8.2
NET_U8_5: U7.6, U8.5
NET_U9_2: C30.1, U9.2
NET_U9_5: C29.1, U9.5
NET_U10_2: C32.1, C33.1, U10.2
NET_U10_5: C31.1, U10.5
NET_U10_13: C32.2, C33.2
NET_U11_1: C34.1, C35.1, C40.1, U7.16, U11.1
NET_U11_15: C34.2, C35.2
NET_U18_4: R27.2, R28.1, U18.4
NET_U19_1: C48.1, U19.1
NET_U19_6: R30.2, R31.1, U19.6
NET_U19_8: R29.1, U19.8
NET_U20_1: C51.1, U20.1
NET_U20_6: R33.2, R34.1, U20.6
NET_U20_8: R32.1, U20.8
NET_U21_1: C54.1, U21.1
NET_U21_6: R36.2, R37.1, U21.6
NET_U21_8: R35.1, U21.8
NET_U22_5: R38.1, U22.5
NET_U22_7: R39.2, R40.1, U22.7
NET_U23_1: R42.1, R43.1, U23.1
NET_U23_3: R44.2, R45.1, U23.3
NET_U23_4: R41.1, U23.4, U26.4, U27.2, U28.2, U29.2
NET_U24_1: R2.1, U24.1, U24.2
PROC_DSIHOST_CKN: U1.86, U4.13
PROC_DSIHOST_CKP: U1.85, U4.14
PROC_DSIHOST_D0N: U1.83, U4.7
PROC_DSIHOST_D0P: U1.82, U4.8
PROC_DSIHOST_D1N: U1.89, U4.10
PROC_DSIHOST_D1P: U1.88, U4.11
PROC_GPIO_TO_U1_USB_FAULT: R14.1, U1.2, U2.6
PROC_GPIO_TO_U1_VBUS_EN: R15.1, U1.1, U2.4
PROC_I2S2_CK: U1.68, U7.24
PROC_I2S2_EXT_SD: U1.23, U7.25
PROC_I2S2_SD: U1.22, U7.26
PROC_I2S2_WS: U1.67, U7.23
PROC_QUADSPI_BK1_IO0: U1.74, U6.5
PROC_QUADSPI_BK1_IO1: U1.75, U6.2
PROC_QUADSPI_BK1_IO2: R24.1, U1.144, U6.3
PROC_QUADSPI_BK1_NCS: R23.1, U1.63, U6.1
PROC_QUADSPI_CLK: U1.17, U6.6
PROC_SYS_JTCK_SWCLK: R17.1, U1.111, U3.4
PROC_SYS_JTDO_SWO: U1.132, U3.6
PROC_SYS_JTMS_SWDIO: R18.1, U1.107, U3.2
PROC_USB_OTG_FS_DM: U1.105, U12.2, U13.3
PROC_USB_OTG_FS_DP: U1.106, U12.3, U13.2
PROC_USB_OTG_FS_ID: U1.104, U12.4
PROC_USB_OTG_FS_VBUS: U1.103, U2.1, U12.1, U13.4
RST_OUT_U3_JTAG_RST_B: R16.1, U3.10, U26.1
VCC_S1_14V1: C44.1, C45.1, C49.1, C52.1, C55.1, C57.1, C60.1, C61.1, J1.1, R29.2, R32.2, R35.2, U18.5, U18.8, U19.4, U20.4, U21.4, U22.8
VCC_TIER1_1V5: C36.1, C46.1, C47.1, R27.1, U4.29, U7.30, U18.1
VCC_TIER1_2V8: C24.1, C25.1, C26.1, C50.1, R30.1, U4.16, U4.21, U4.22, U4.23, U19.5
VCC_TIER1_3V3: C1.1, C2.1, C3.1, C4.1, C5.1, C6.1, C7.1, C8.1, C9.1, C10.1, C11.1, C12.1, C13.1, C14.1, C19.1, C21.1, C22.1, C27.1, C28.1, C37.1, C38.1, C41.1, C42.1, C43.1, C53.1, C59.1, C62.1, C63.1, C64.1, C65.1, F1.2, R4.2, R5.2, R6.2, R7.2, R8.2, R9.2, R11.2, R12.2, R14.2, R16.2, R17.2, R18.2, R21.2, R22.2, R23.2, R24.2, R25.2, R33.1, R41.2, R42.2, R44.1, U1.5, U1.16, U1.25, U1.34, U1.46, U1.56, U1.66, U1.77, U1.80, U1.97, U1.110, U1.123, U1.130, U1.143, U3.1, U4.2, U5.14, U6.8, U7.5, U7.20, U15.4, U16.4, U17.4, U20.5, U23.6, U26.5, U27.5, U28.5, U29.5
VCC_TIER1_5V0: C56.1, R36.1, U2.5, U21.5
VCC_TIER1_12V0: C23.1, C58.1, R38.2, R39.1, U4.30, U22.1
